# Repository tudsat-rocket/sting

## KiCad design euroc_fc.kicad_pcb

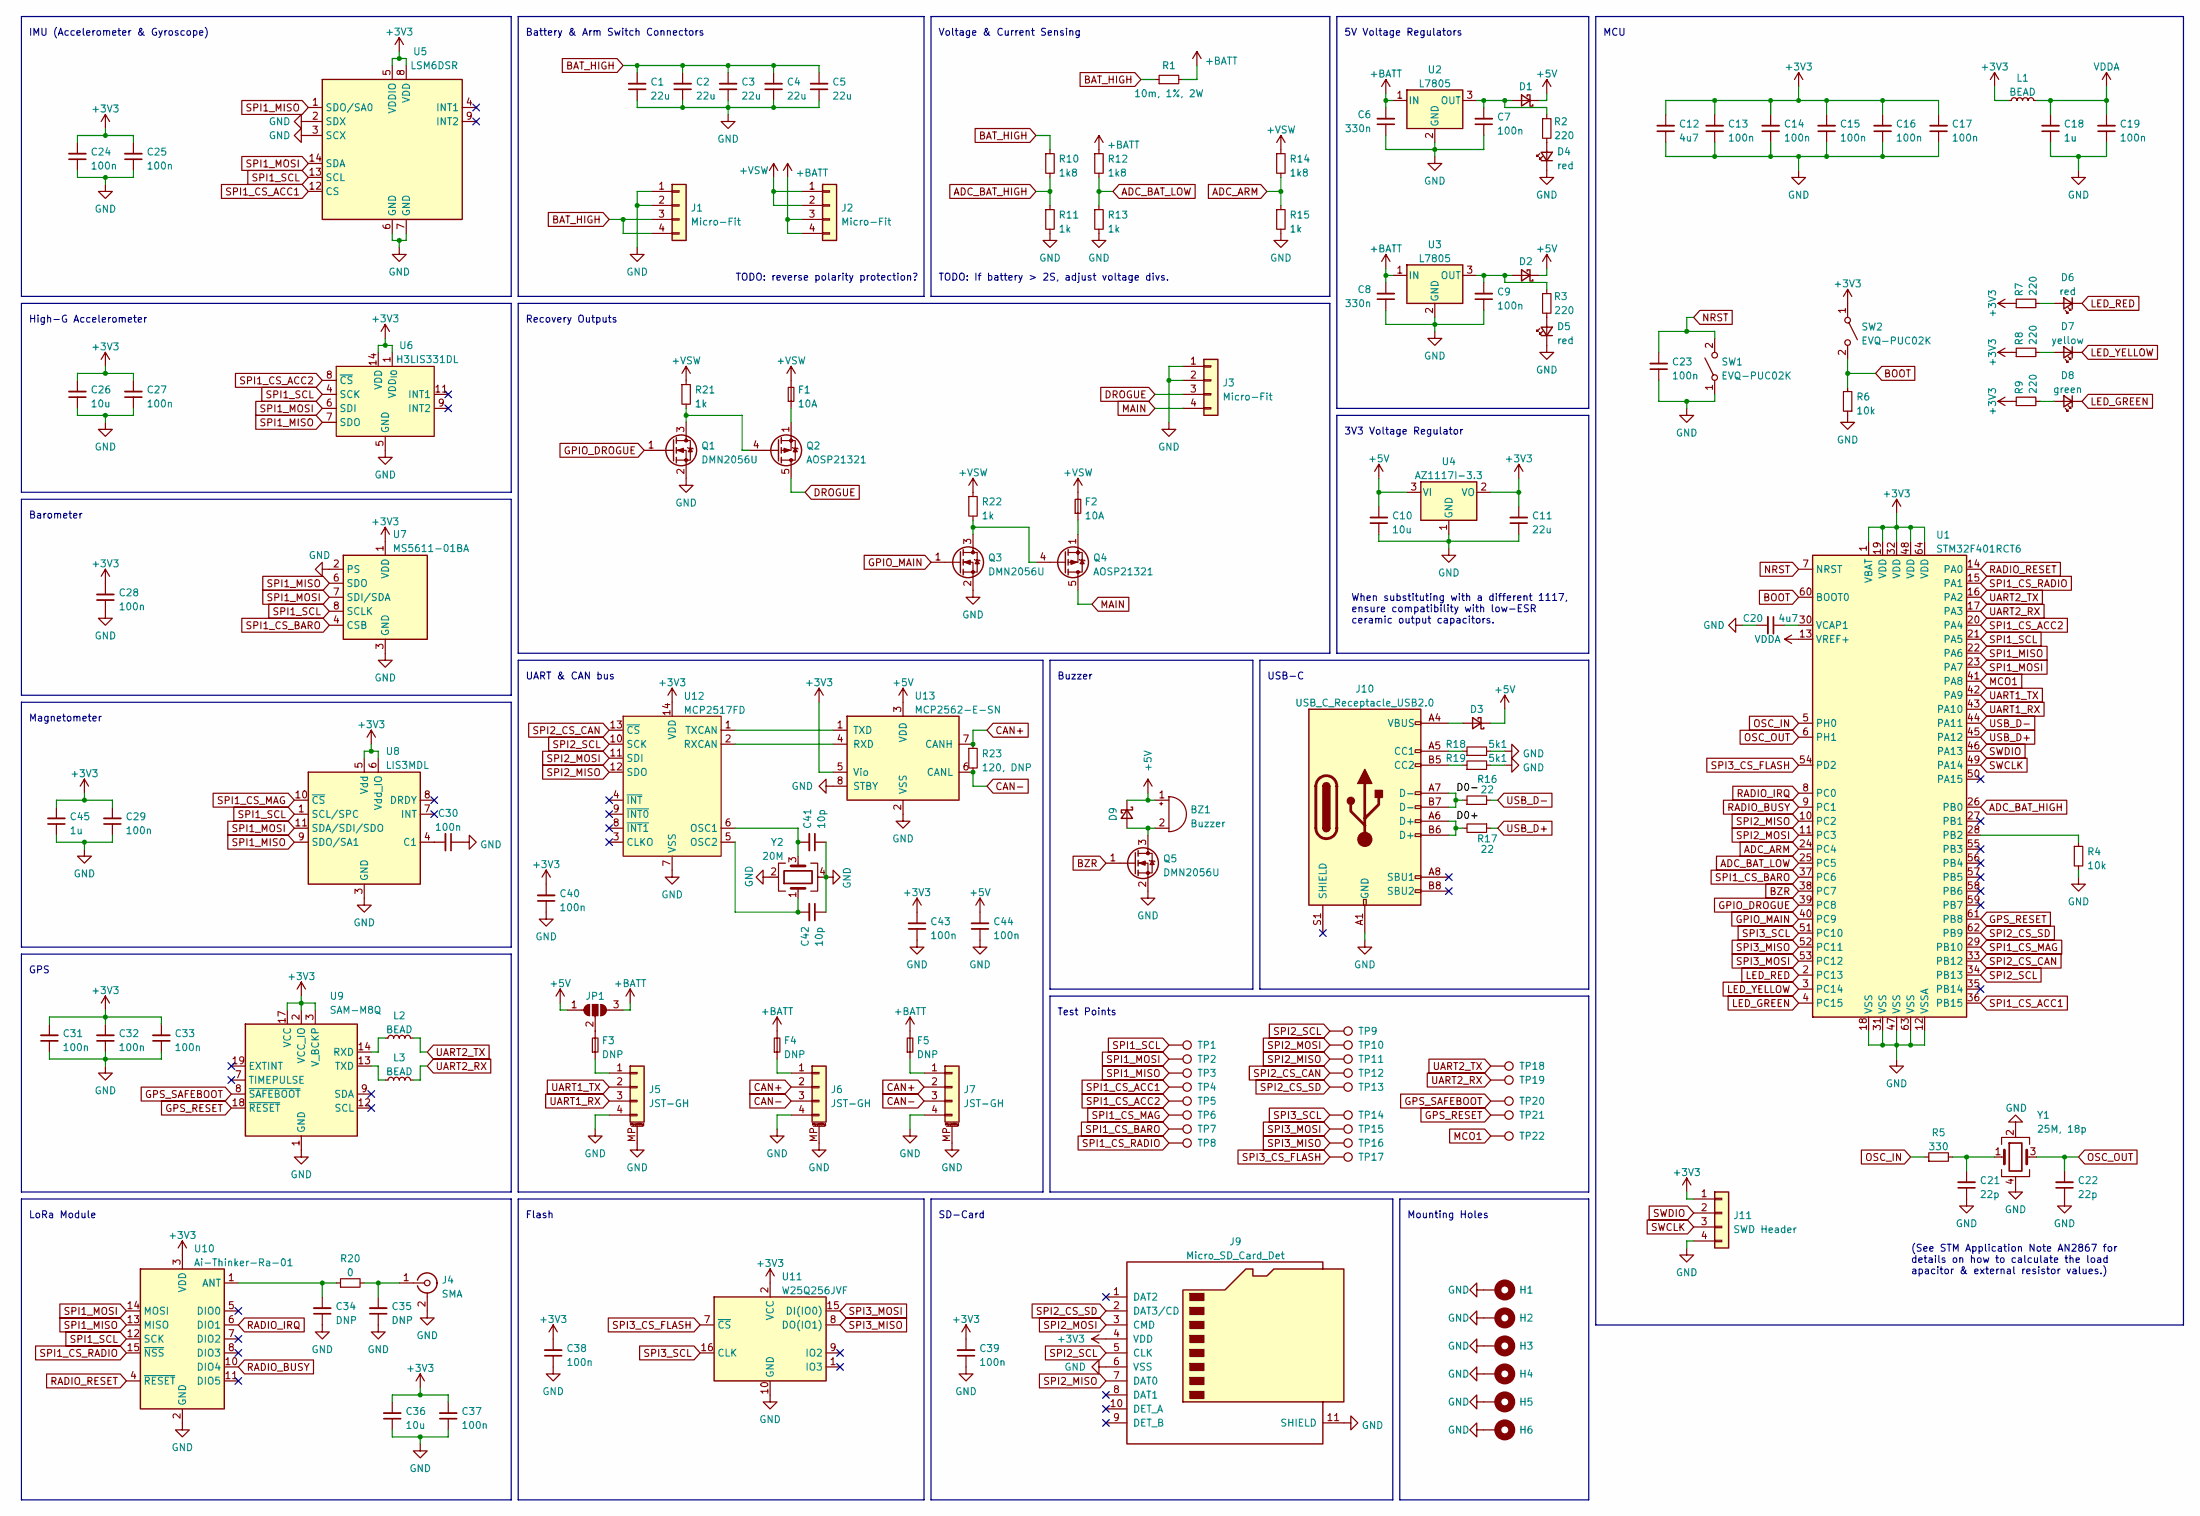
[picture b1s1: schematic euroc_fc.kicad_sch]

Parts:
BZ1: Buzzer; MagneticBuzzer_CUI_CMT-8504-100-SMT; Part# CMT-8504-100-SMT-TR; DigiKey# 102-CMT-8504-100-SMT-CT-ND
C1, C2, C3, C4, C5, C11: 22u; C_1206_3216Metric; Part# CL31A226KAHNNNE; LCSC# C12891
C6, C8: 330n; C_0603_1608Metric; Part# CL10B334KO8NNNC; LCSC# C159798
C7, C9, C13, C14, C15, C16, C17, C19, C23, C24, C25, C27, C28, C29, C30, C31, C32, C33, C37, C38, C39, C40, C43, C44: 100n; C_0603_1608Metric; Part# CL10B104KB8NNNC; LCSC# C1591
C10, C26, C36: 10u; C_1206_3216Metric; Part# CL31B106KAHNNNE; LCSC# C14860
C12, C20: 4u7; C_1206_3216Metric; Part# CL31B475KAHNNNE; LCSC# C1872
C18, C45: 1u; C_0805_2012Metric; Part# CL21A105KBCLNNC; LCSC# C318694
C21, C22: 22p; C_0603_1608Metric; Part# CL10C220JB8NNNC; LCSC# C1653
C34, C35: DNP; C_0603_1608Metric; Part# N/A; DigiKey# N/A
C41, C42: 10p; C_0603_1608Metric; Part# CL10C100JB8NNNC; LCSC# C1634
D1, D2, D3, D9: D_SOD-123F; Part# PMEG3020EH,115; LCSC# C167645
D4, D5, D6: red; LED_0603_1608Metric; Part# 19-213/RSC-BS2T2B/3T; LCSC# C474026
D7: yellow; LED_0603_1608Metric; Part# 19-213/Y2C-CQ2R2L/3T(CY); LCSC# C72038
D8: green; LED_0603_1608Metric; Part# 19-217/GHC-YR1S2/3T; LCSC# C72043
F1, F2: 10A; Fuse_1206_3216Metric; Part# 0501010.WR1; LCSC# C207003
F3, F4, F5: DNP; Fuse_1206_3216Metric; Part# N/A; DigiKey# N/A
H1, H2, H3, H4, H5, H6: MountingHole_Pad; MountingHole_3.2mm_M3_Pad_Via; Part# N/A; DigiKey# N/A
J1, J2, J3: Micro-Fit; Molex_Micro-Fit_3.0_43045-0400_2x02_P3.00mm_Horizontal; Part# 0430450400; LCSC# C122413
J4: SMA; SMA_Amphenol_901-143_Horizontal; Part# KH-SMA-K513-G; LCSC# C411575
J5, J6, J7: JST-GH; JST_GH_SM04B-GHS-TB_1x04-1MP_P1.25mm_Horizontal; Part# SM04B-GHS-TB; LCSC# C189895
J9: Micro_SD_Card_Det; microSD_HC_Hirose_DM3AT-SF-PEJM5; Part# DM3AT-SF-PEJM5; LCSC# C114218
J10: USB_C_Receptacle_USB2.0; USB_C_Receptacle_Palconn_UTC16-G; Part# KH-TYPE-C-16P; LCSC# C709357
J11: SWD Header; PinHeader_1x04_P2.54mm_Vertical
JP1: SolderJumper_3_Open; SolderJumper-3_P1.3mm_Open_RoundedPad1.0x1.5mm_NumberLabels; Part# N/A; DigiKey# N/A
L1, L2, L3: BEAD; L_0603_1608Metric; Part# BLM18AG601SN1D; LCSC# C19330
Q1, Q3, Q5: DMN2056U; SOT-23; Part# DMN2056U-7; LCSC# C332302
Q2, Q4: AOSP21321; SO-8_3.9x4.9mm_P1.27mm; Part# AOSP21321; LCSC# C560863
R1: 10m, 1%, 2W; R_2512_6332Metric; Part# PA2512FKE7W0R01E; LCSC# C375688
R2, R3, R7, R8, R9: 220; R_0603_1608Metric; Part# ESR03EZPJ221; LCSC# C2085669
R4, R6: 10k; R_0603_1608Metric; Part# RC0603FR-0710KL; LCSC# C98220
R5: 330; R_0603_1608Metric; Part# RC0603FR-07330RL; LCSC# C105881
R10, R12, R14: 1k8; R_0603_1608Metric; Part# RC0603FR-071K8L; LCSC# C185354
R11, R13, R15, R21, R22: 1k; R_0603_1608Metric; Part# RC0603FR-071KL; LCSC# C22548
R16, R17: 22; R_0603_1608Metric; Part# RC0603FR-0722RL; LCSC# C107701
R18, R19: 5k1; R_0603_1608Metric; Part# RC0603FR-075K1L; LCSC# C105580
R20: 0; R_0603_1608Metric; Part# RC0603FR-070RL; LCSC# C100044
R23: 120, DNP; R_0603_1608Metric; Part# RC0603FR-07120RL; LCSC# C114640
SW1, SW2: EVQ-PUC02K; Panasonic_EVQPUL_EVQPUC; Part# EVQPUC02K; LCSC# C79174
TP1, TP2, TP3, TP4, TP5, TP6, TP7, TP8, TP9, TP10, TP11, TP12, TP13, TP14, TP15, TP16, TP17, TP18, TP19, TP20, TP21, TP22: TestPoint; TestPoint_Pad_D2.0mm; Part# N/A; DigiKey# N/A
U1: STM32F401RCT6; LQFP-64_10x10mm_P0.5mm; Part# STM32F401RCT6; LCSC# C74524
U2, U3: L7805; TO-252-2; Part# L7805CDT-TR; LCSC# C310413
U4: AZ1117I-3.3; SOT-223-3_TabPin2; Part# AZ1117CH-3.3TRG1; LCSC# C92102
U5: LSM6DSR; LGA-14_3x2.5mm_P0.5mm_LayoutBorder3x4y; Part# LSM6DSRTR; LCSC# C784817
U6: H3LIS331DL; LGA-16_3x3mm_P0.5mm_LayoutBorder3x5y; Part# H3LIS331DLTR; DigiKey# 497-13903-1-ND
U7: MS5611-01BA; LGA-8_3x5mm_P1.25mm; Part# MS561101BA03-50; DigiKey# 223-1622-1-ND
U8: LIS3MDL; LGA-12_2x2mm_P0.5mm; Part# LIS3MDLTR; DigiKey# 497-13892-1-ND
U9: SAM-M8Q; ublox_SAM-M8Q; Part# SAM-M8Q-0-10; DigiKey# 672-1054-1-ND
U10: Ai-Thinker-Ra-01; Ai-Thinker-Ra-01-LoRa; Part# Ra-01SC; LCSC# C2830749
U11: W25Q256JVF; SOIC-16W_7.5x10.3mm_P1.27mm; Part# W25Q256JVFIQ; DigiKey# W25Q256JVFIQ-ND
U12: MCP2517FD; SOIC-14_3.9x8.7mm_P1.27mm; Part# MCP2517FDT-H/SL; DigiKey# MCP2517FDT-H/SLCT-ND
U13: MCP2562-E-SN; SOIC-8_3.9x4.9mm_P1.27mm; Part# MCP2562-H/SN; DigiKey# MCP2562-H/SN
Y1: 25M, 18p; Oscillator_SMD_SeikoEpson_SG210-4Pin_2.5x2.0mm; Part# Q24FA20H0039000; LCSC# C255956
Y2: 20M; Crystal_SMD_2016-4Pin_2.0x1.6mm; Part# Q22FA12800335; LCSC# C255878

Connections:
+3V3: C11.2, C12.2, C13.2, C14.2, C15.2, C16.2, C17.2, C24.2, C25.2, C26.2, C27.2, C28.2, C29.2, C31.2, C32.2, C33.2, C36.2, C37.2, C38.2, C39.2, C40.2, C43.2, C45.2, J9.4 (VDD), J11.1, L1.1, R7.1, R8.1, R9.1, SW2.1 (A), U1.1 (VBAT), U1.19 (VDD), U1.32 (VDD), U1.48 (VDD), U1.64 (VDD), U4.2 (VO), U5.5 (VDDIO), U5.8 (VDD), U6.1 (VDD_{IO}), U6.14 (VDD), U6.15 (reserved), U7.1 (VDD), U8.5 (Vdd), U8.6 (Vdd_IO), U9.2 (VCC_IO), U9.3 (V_BCKP), U9.17 (VCC), U10.3 (VDD), U11.2 (VCC), U12.14 (VDD), U13.5 (Vio)
+5V: BZ1.1 (-), C10.2, C44.2, D1.1 (K), D2.1 (K), D3.1 (K), D9.1 (K), JP1.1 (A), U4.3 (VI), U13.3 (VDD)
+BATT: C6.2, C8.2, F4.2, F5.2, J2.3, J2.4, JP1.3 (B), R1.2, R12.1, U2.1 (IN), U3.1 (IN)
+VSW: F1.2, F2.2, J2.1, J2.2, R14.1, R21.1, R22.1
/D0+: J10.A6 (D+), J10.B6 (D+), R17.2
/D0-: J10.A7 (D-), J10.B7 (D-), R16.1
ADC_ARM: R14.2, R15.1, U1.24 (PC4)
ADC_BAT_HIGH: R10.2, R11.1, U1.26 (PB0)
ADC_BAT_LOW: R12.2, R13.1, U1.25 (PC5)
BAT_HIGH: C1.2, C2.2, C3.2, C4.2, C5.2, J1.3, J1.4, R1.1, R10.1
BOOT: R6.2, SW2.2 (B), U1.60 (BOOT0)
BZR: Q5.1 (G), U1.38 (PC7)
CAN+: J6.2, J7.2, R23.1, U13.7 (CANH)
CAN-: J6.3, J7.3, R23.2, U13.6 (CANL)
DROGUE: J3.3, Q2.5 (D), Q2.6 (D), Q2.7 (D), Q2.8 (D)
GND: C1.1, C2.1, C3.1, C4.1, C5.1, C6.1, C7.1, C8.1, C9.1, C10.1, C11.1, C12.1, C13.1, C14.1, C15.1, C16.1, C17.1, C18.1, C19.1, C20.2, C21.1, C22.1, C23.1, C24.1, C25.1, C26.1, C27.1, C28.1, C29.1, C30.1, C31.1, C32.1, C33.1, C34.1, C35.1, C36.1, C37.1, C38.1, C39.1, C40.1, C41.1, C42.1, C43.1, C44.1, C45.1, D4.1 (K), D5.1 (K), H1.1, H2.1, H3.1, H4.1, H5.1, H6.1, J1.1, J1.2, J3.1, J3.2, J4.2 (Ext), J5.4, J5.MP (MountPin), J6.4, J6.MP (MountPin), J7.4, J7.MP (MountPin), J9.6 (VSS), J9.11 (SHIELD), J10.A1 (GND), J10.A12 (GND), J10.B1 (GND), J10.B12 (GND), J11.4, Q1.2 (S), Q3.2 (S), Q5.2 (S), R4.2, R6.1, R11.2, R13.2, R15.2, R18.2, R19.2, SW1.1 (A), U1.12 (VSSA), U1.18 (VSS), U1.31 (VSS), U1.47 (VSS), U1.63 (VSS), U2.2 (GND), U3.2 (GND), U4.1 (GND), U5.2 (SDX), U5.3 (SCX), U5.6 (GND), U5.7 (GND), U6.5 (GND), U6.10 (reserved), U6.12 (GND), U6.13 (GND), U6.16 (GND), U7.2 (PS), U7.3 (GND), U8.2 (GND), U8.3 (GND), U8.12 (GND), U9.1 (GND), U9.4 (GND), U9.5 (GND), U9.6 (GND), U9.10 (GND), U9.11 (GND), U9.15 (GND), U9.16 (GND), U9.20 (GND), U10.2 (GND), U10.9 (GND), U10.16 (GND), U11.10 (GND), U12.7 (VSS), U13.2 (VSS), U13.8 (STBY), Y1.2, Y1.4, Y2.2, Y2.4
GPIO_DROGUE: Q1.1 (G), U1.39 (PC8)
GPIO_MAIN: Q3.1 (G), U1.40 (PC9)
GPS_RESET: TP21.1, U1.61 (PB8), U9.18 (~RESET)
GPS_SAFEBOOT: TP20.1, U9.8 (~SAFEBOOT)
LED_GREEN: D8.1 (K), U1.4 (PC15)
LED_RED: D6.1 (K), U1.2 (PC13)
LED_YELLOW: D7.1 (K), U1.3 (PC14)
MAIN: J3.4, Q4.5 (D), Q4.6 (D), Q4.7 (D), Q4.8 (D)
MCO1: TP22.1, U1.41 (PA8)
NRST: C23.2, SW1.2 (B), U1.7 (NRST)
unnamed: BZ1.2 (+), D9.2 (A), Q5.3 (D)
unnamed: C7.2, D1.2 (A), R2.1, U2.3 (OUT)
unnamed: C9.2, D2.2 (A), R3.1, U3.3 (OUT)
unnamed: C20.1, U1.30 (VCAP1)
unnamed: C21.2, R5.2, Y1.1
unnamed: C30.2, U8.4 (C1)
unnamed: C34.2, R20.1, U10.1 (ANT)
unnamed: C35.2, J4.1 (In), R20.2
unnamed: C41.2, U12.6 (OSC1), Y2.3
unnamed: C42.2, U12.5 (OSC2), Y2.1
unnamed: D3.2 (A), J10.A4 (VBUS), J10.A9 (VBUS), J10.B4 (VBUS), J10.B9 (VBUS)
unnamed: D4.2 (A), R2.2
unnamed: D5.2 (A), R3.2
unnamed: D6.2 (A), R7.2
unnamed: D7.2 (A), R8.2
unnamed: D8.2 (A), R9.2
unnamed: F1.1, Q2.1 (S), Q2.2 (S), Q2.3 (S)
unnamed: F2.1, Q4.1 (S), Q4.2 (S), Q4.3 (S)
unnamed: F3.1, J5.1
unnamed: F3.2, JP1.2 (C)
unnamed: F4.1, J6.1
unnamed: F5.1, J7.1
unnamed: J10.A5 (CC1), R18.1
unnamed: J10.B5 (CC2), R19.1
unnamed: L2.1, U9.14 (RXD)
unnamed: L3.1, U9.13 (TXD)
unnamed: Q1.3 (D), Q2.4 (G), R21.2
unnamed: Q3.3 (D), Q4.4 (G), R22.2
unnamed: R4.1, U1.28 (PB2)
unnamed: U12.1 (TXCAN), U13.1 (TXD)
unnamed: U12.2 (RXCAN), U13.4 (RXD)
OSC_IN: R5.1, U1.5 (PH0)
OSC_OUT: C22.2, U1.6 (PH1), Y1.3
RADIO_BUSY: U1.9 (PC1), U10.10 (DIO4)
RADIO_IRQ: U1.8 (PC0), U10.6 (DIO1)
RADIO_RESET: U1.14 (PA0), U10.4 (~RESET)
SPI1_CS_ACC1: TP4.1, U1.36 (PB15), U5.12 (CS)
SPI1_CS_ACC2: TP5.1, U1.20 (PA4), U6.8 (~CS)
SPI1_CS_BARO: TP7.1, U1.37 (PC6), U7.4 (CSB), U7.5 (CSB)
SPI1_CS_MAG: TP6.1, U1.29 (PB10), U8.10 (~CS)
SPI1_CS_RADIO: TP8.1, U1.15 (PA1), U10.15 (~NSS)
SPI1_MISO: TP3.1, U1.22 (PA6), U5.1 (SDO/SA0), U6.7 (SDO), U7.6 (SDO), U8.9 (SDO/SA1), U10.13 (MISO)
SPI1_MOSI: TP2.1, U1.23 (PA7), U5.14 (SDA), U6.6 (SDI), U7.7 (SDI/SDA), U8.11 (SDA/SDI/SDO), U10.14 (MOSI)
SPI1_SCL: TP1.1, U1.21 (PA5), U5.13 (SCL), U6.4 (SCK), U7.8 (SCLK), U8.1 (SCL/SPC), U10.12 (SCK)
SPI2_CS_CAN: TP12.1, U1.33 (PB12), U12.13 (~CS)
SPI2_CS_SD: J9.2 (DAT3/CD), TP13.1, U1.62 (PB9)
SPI2_MISO: J9.7 (DAT0), TP11.1, U1.10 (PC2), U12.12 (SDO)
SPI2_MOSI: J9.3 (CMD), TP10.1, U1.11 (PC3), U12.11 (SDI)
SPI2_SCL: J9.5 (CLK), TP9.1, U1.34 (PB13), U12.10 (SCK)
SPI3_CS_FLASH: TP17.1, U1.54 (PD2), U11.7 (~CS)
SPI3_MISO: TP16.1, U1.52 (PC11), U11.8 (DO(IO1))
SPI3_MOSI: TP15.1, U1.53 (PC12), U11.15 (DI(IO0))
SPI3_SCL: TP14.1, U1.51 (PC10), U11.16 (CLK)
SWCLK: J11.3, U1.49 (PA14)
SWDIO: J11.2, U1.46 (PA13)
UART1_RX: J5.3, U1.43 (PA10)
UART1_TX: J5.2, U1.42 (PA9)
UART2_RX: L3.2, TP19.1, U1.17 (PA3)
UART2_TX: L2.2, TP18.1, U1.16 (PA2)
USB_D+: R17.1, U1.45 (PA12)
USB_D-: R16.2, U1.44 (PA11)
VDDA: C18.2, C19.2, L1.2, U1.13 (VREF+)

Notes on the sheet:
SD-Card
High-G Accelerometer
Magnetometer
GPS
Recovery Outputs
USB-C
Mounting Holes
Battery & Arm Switch Connectors
When substituting with a different 1117, ensure compatibility with low-ESR ceramic output capacitors.
Voltage & Current Sensing
Barometer
Flash
IMU (Accelerometer & Gyroscope)
LoRa Module
Test Points
Buzzer
TODO: reverse polarity protection?
TODO: If battery > 2S, adjust voltage divs.
UART & CAN bus
(See STM Application Note AN2867 for details on how to calculate the load apacitor & external resistor values.)
5V Voltage Regulators
MCU
3V3 Voltage Regulator

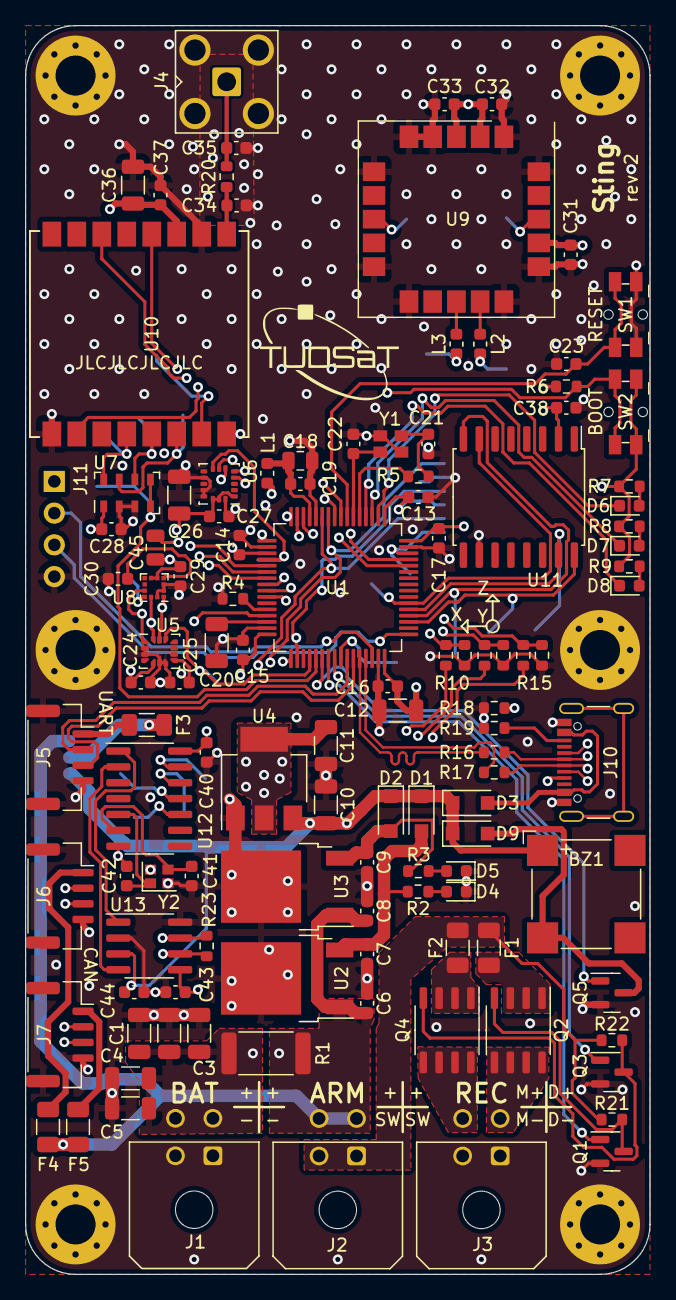
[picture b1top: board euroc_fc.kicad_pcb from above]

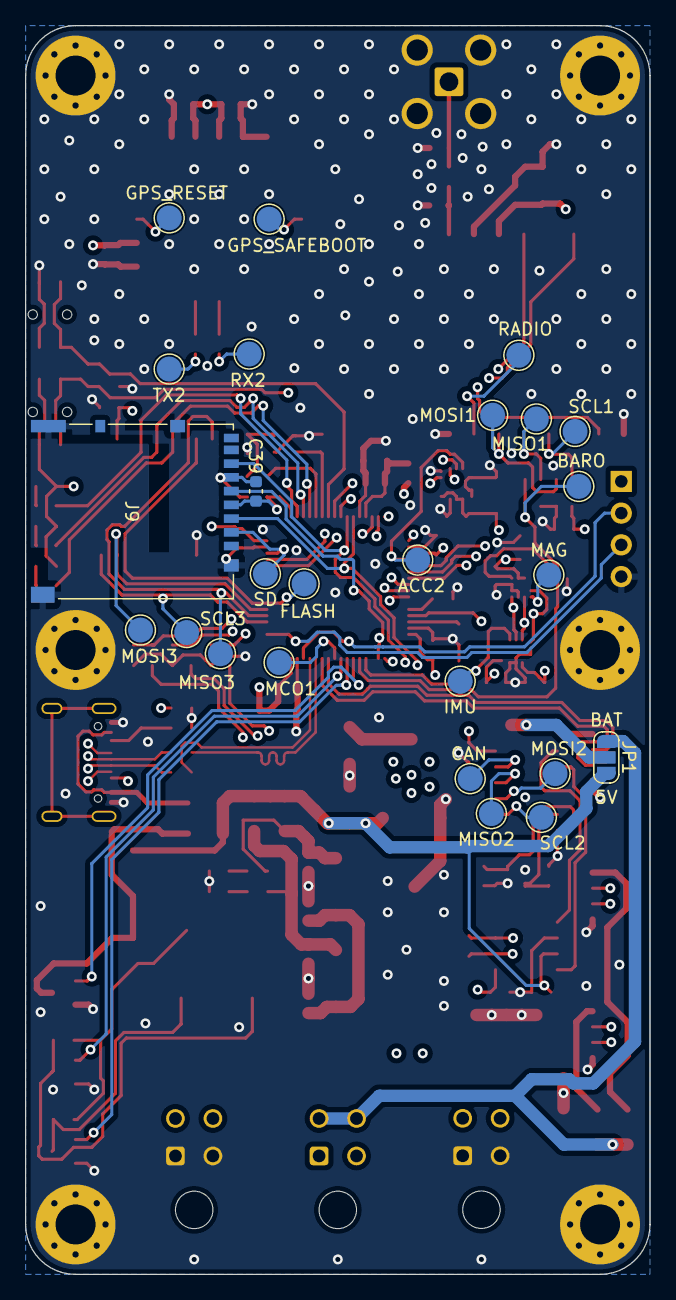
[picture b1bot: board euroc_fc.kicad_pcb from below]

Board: 4 copper layers, 50.0 x 100.0 mm, 147 parts (25 on the bottom side), 88 nets.

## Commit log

2022-07-01 Update part selection, complete BOM
    - Voltage divider reduced to 1k / (1k + 1k8)
    - Diode changed to onsemi SS26FL (higher current capacity)
    - N-Ch. MOSFET changed to DMN2056U (official successor)
    - uSD holder changed to Hirose DM3AT (push-push)
    - Vendor and Datasheet fields filled out for (almost) all components
2022-07-09 Tweak LoRa trans line impedance, power planes
2022-07-09 Tweak via grouping for power planes
2022-07-09 Add flyback diode for buzzer
2022-07-09 Fix ADC pin assignment, rename nets
2022-07-10 Place additional test points
2022-07-10 Tweak test points
2022-07-12 Remove various TODOs
2022-07-14 Relayout the board, optimize return current paths
    - Board stackup changed to Signal, Ground, Signal+Power, Signal+Ground
    - L2 is now uninterrupted ground plane
    - Addition of a proper SWD header (SWD test points removed)
    - Moved all auxilliary connectors to the left
    - Optimized paths for high-speed signals (SPI, SWD, USB)
    - All SPI1 devices grouped on the left, SPI2 & 3 on the right, meaning
2022-07-26 Adjust cap value notation
2022-07-26 Restructure BOM
2022-07-26 Replace crystal oscillator part
2022-07-26 Replace USB connector
    New part is cheaper, smaller, easier to solder and avilable at LCSC.
    Also, don't ground the USB shield anymore.
2022-07-26 Substitute various parts with LCSC alternatives
2022-07-26 Update BOM
2022-09-08 Fix MCO typo
2023-01-26 Add CAN bus controller, transceiver & connectors
    - Accelerometer 2 is removed from SPI for now, to be replaced
    - Flash moved from SPI2 to SPI3
    - SPI2 is used for CAN bus (also SD Card)
    - ADC voltage dividers moved to right of PCB, IO connectors removed to
    make room
    - Minor pinout changes.
2023-01-26 Replace backup acc., magnetometer
2023-01-26 Update 3dmodels to step
2023-02-12 Finish rev. 2
2023-02-13 Update BOM for rev. 2
